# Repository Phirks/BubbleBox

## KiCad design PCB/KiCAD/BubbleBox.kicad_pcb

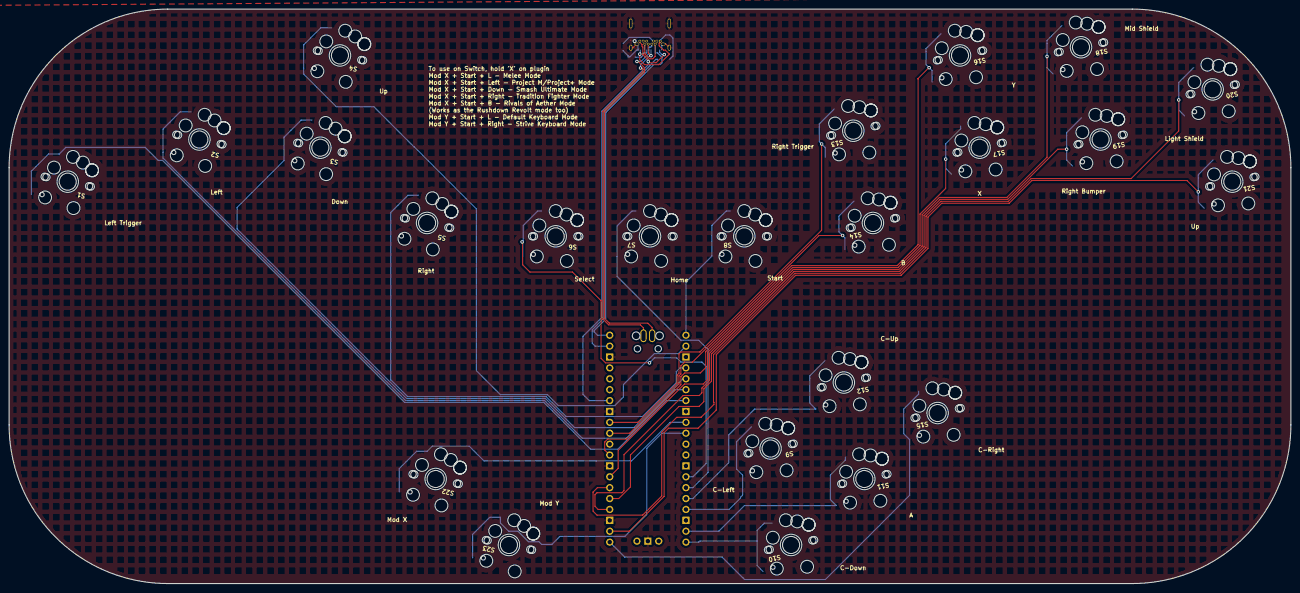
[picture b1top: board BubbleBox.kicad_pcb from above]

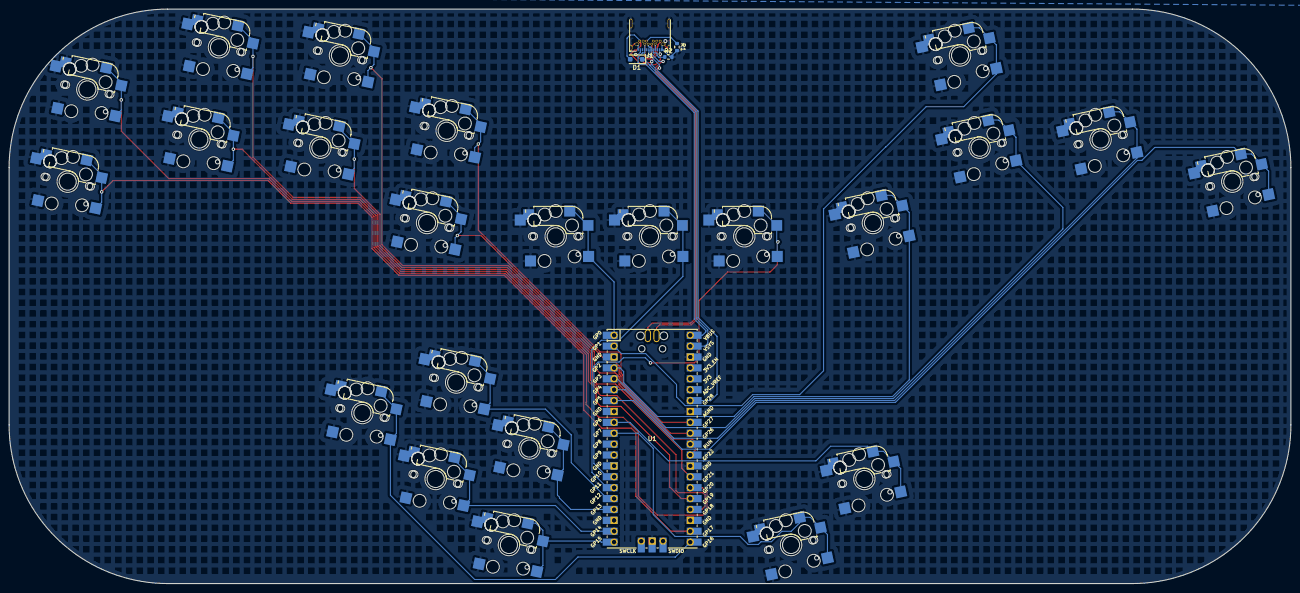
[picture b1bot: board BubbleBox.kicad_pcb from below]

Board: 2 copper layers, 299.0 x 134.0 mm, 28 parts (5 on the bottom side), 32 nets.

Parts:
D1: D_Schottky; D_SOD-123F
J1: USB_C_Receptacle; USB-C_port_HC-TYPE-C-24P-DS10.0-CH2.75S-5A-04
R1, R2: 5K1; R_0603_1608Metric
S1, S2, S3, S4, S5, S6, S7, S8, S9, S10, S11, S12, S13, S14, S15, S16, S17, S18, S19, S20, S21, S22, S23: Keyswitch; gateron-ks27-choc-v1-mx-hotswap
U1: Pi_Pico; RPi_Pico_SMD_TH

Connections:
A: S11.2, U1.19 (GPIO14)
B: S14.2, U1.31 (GPIO26_ADC0)
C-Down: S10.2, U1.20 (GPIO15)
C-Left: S9.2, U1.17 (GPIO13)
C-Right: S15.2, U1.21 (GPIO16)
C-Up: S12.2, U1.16 (GPIO12)
D+: J1.A6 (D+), J1.B6 (D+), U1.44 (D+)
D-: J1.A7 (D-), J1.B7 (D-), U1.45 (D-)
Down: S3.2, U1.5 (GPIO3)
GCD: J1.A11 (RX2+), J1.B11 (RX1+), U1.34 (GPIO28_ADC2)
GND: J1.A1 (GND), J1.A12 (GND), J1.B1 (GND), J1.B12 (GND), J1.S1 (SHIELD), R1.2, R2.2, S1.1, S2.1, S3.1, S4.1, S5.1, S6.1, S7.1, S8.1, S9.1, S10.1, S11.1, S12.1, S13.1, S14.1, S15.1, S16.1, S17.1, S18.1, S19.1, S20.1, S21.1, S22.1, S23.1, U1.23 (GND), U1.28 (GND), U1.33 (AGND), U1.38 (GND), U1.42 (GND)
Home: S7.2, U1.15 (GPIO11)
Left: S2.2, U1.6 (GPIO4)
Left Trigger: S1.2, U1.7 (GPIO5)
Light Shield (LS): S20.2, U1.26 (GPIO20)
Mid Shield (MS): S18.2, U1.24 (GPIO18)
Mod X: S22.2, U1.9 (GPIO6)
Mod Y: S23.2, U1.10 (GPIO7)
unnamed: D1.2 (A), J1.A2 (TX1+), J1.B2 (TX2+)
unnamed: J1.A5 (CC1), R2.1
unnamed: J1.B5 (CC2), R1.1
Right: S5.2, U1.4 (GPIO2)
Right Bumper (Z): S19.2, U1.25 (GPIO19)
Right Trigger (R): S13.2, U1.32 (GPIO27_ADC1)
Select: S6.2, U1.14 (GPIO10)
Start: S8.2, U1.1 (GPIO0)
Up1: S21.2, U1.22 (GPIO17)
Up2: S4.2, U1.2 (GPIO1)
VBUS: J1.A4 (VBUS), J1.A9 (VBUS), J1.B4 (VBUS), J1.B9 (VBUS), U1.40 (VBUS)
VSYS: D1.1 (K), U1.39 (VSYS)
X: S17.2, U1.27 (GPIO21)
Y: S16.2, U1.29 (GPIO22)

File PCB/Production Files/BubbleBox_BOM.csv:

"Reference","Value","Qty","DNP","Manufacturer","Part Number","Price","Vendor","Website"
"R1,R2","5K1","2","","FOJAN","FRC0603J512 TS",".0008","LCSC","https://www.lcsc.com/product-detail/Chip-Resistor-Surface-Mo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"
"D1","D_Schottky","1","","GOODWORK","B5819WL",".0104","LCSC","https://www.lcsc.com/product-detail/Schottky-Diodes_GOODWORK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"
"J1","USB_C_Receptacle","1","","HCTL","HC-TYPE-C-24P-DS10.0-CH2.75S-5A-04",".24","LCSC","https://www.lcsc.com/product-detail/USB-Connectors_HCTL-HC-T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"
"U1","Pi_Pico","1","","Raspberry Pi","PICO","6.44","LCSC","https://www.lcsc.com/product-detail/Raspberry-Pi_Raspberry-P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"
"S1,S2,S3,S4,S5,S6,S7,S8,S9,S10,S11,S12,S13,S14,S15,S16,S17,S18,S19,S20,S21,S22,S23","Keyswitch_Hotswap","23","","Gateron","KS-2P02B01-02",".10","Gateron","https://www.gateron.com/products/gateron-low-profile-switch-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"

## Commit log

2025-01-09 Created PCB for easier DIY assembly
